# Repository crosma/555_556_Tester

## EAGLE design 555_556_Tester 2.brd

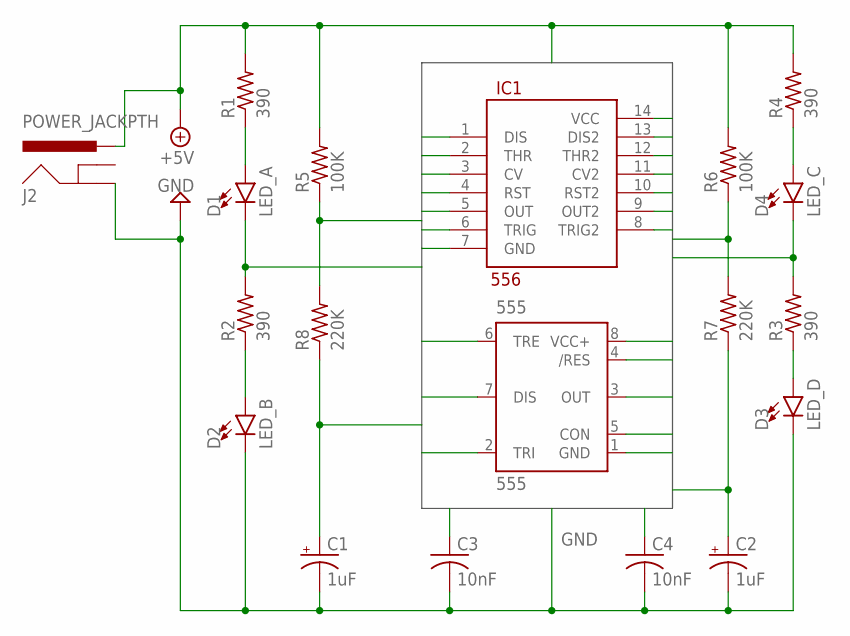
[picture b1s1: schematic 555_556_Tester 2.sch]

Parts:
555: 555; DIP08-KIT
C1, C2: 1uF; E2-4
C3, C4: 10nF; C025-025X050
D1: LED_A; LED_3MM
D2: LED_B; LED_3MM
D3: LED_D; LED_3MM
D4: LED_C; LED_3MM
IC1: 556; DIL14-KIT
J2: POWER_JACKPTH; POWER_JACK_PTH
R1, R2, R3, R4: 390; 0204/5
R5, R6: 100K; 0204/5
R7, R8: 220K; 0204/5

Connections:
+5V: 555.4 (/RES), 555.8 (VCC+), IC1.4 (RST), IC1.10 (RST2), IC1.14 (VCC), J2.PWR, R1.2, R4.2, R5.2, R6.2
CV: 555.5 (CON), C3.1, IC1.3 (CV)
CV2: C4.1, IC1.11 (CV2)
DIS: 555.7 (DIS), IC1.1 (DIS), R5.1, R8.2
DIS2: IC1.13 (DIS2), R6.1, R7.2
GND: 555.1 (GND), C1.-, C2.-, C3.2, C4.2, D2.K (C), D3.K (C), IC1.7 (GND), J2.GND
unnamed: D1.A, R1.1
unnamed: D2.A, R2.1
unnamed: D3.A, R3.1
unnamed: D4.A, R4.1
OUT: 555.3 (OUT), D1.K (C), IC1.5 (OUT), R2.2
OUT2: D4.K (C), IC1.9 (OUT2), R3.2
THR2_TRIG2: C2.+, IC1.8 (TRIG2), IC1.12 (THR2), R7.1
THR_TRIG: 555.2 (TRI), 555.6 (TRE), C1.+, IC1.2 (THR), IC1.6 (TRIG), R8.1

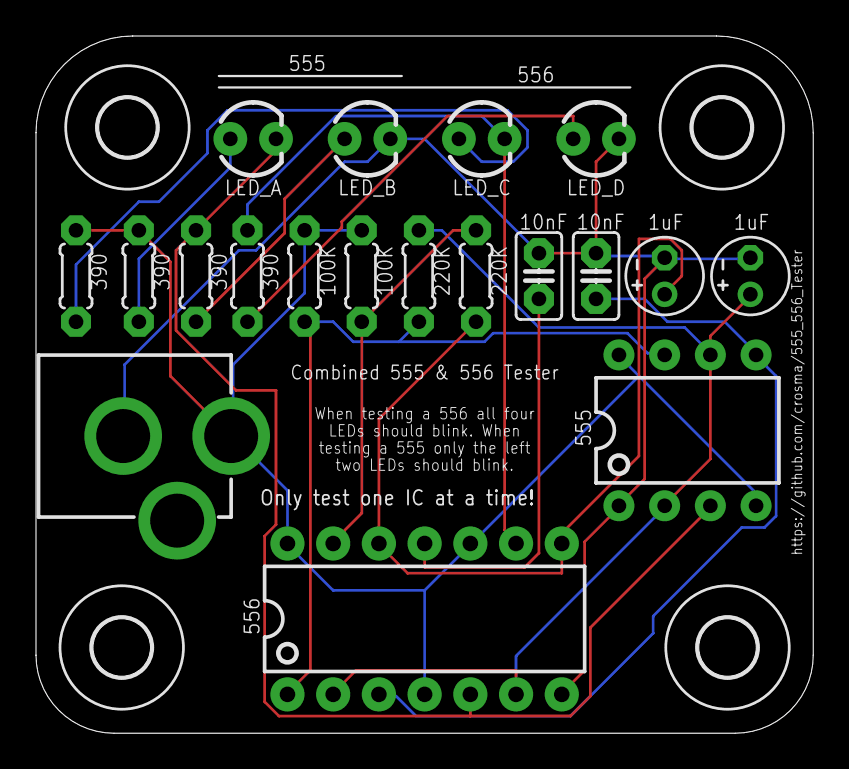
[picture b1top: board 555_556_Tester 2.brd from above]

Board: 2 copper layers, 43.2 x 38.7 mm, 23 parts (0 on the bottom side), 14 nets.

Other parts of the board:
U$1, U$2, U$3, U$4: 3,2

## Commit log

2017-04-07 Revisions

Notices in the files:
parts and their libraries:
SparkFun-LED: Licensing: Creative Commons ShareAlike 4.0 International - https://creativecommons.org/licenses/by-sa/4.0
